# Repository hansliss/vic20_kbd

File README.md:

# vic20_kbd
A Cherry MX based keyboard for the VIC-20/C64, using the same matrix/interface, and aiming for the same form factor.

SHIFT LOCK is implemented with a flip-flop instead of a toggling switch.

The anti-ghosting diodes are probably not really needed, I just thought it SHOULD have them. Have fun soldering!

I use a normal 2.54mm pitch single-row pin header socket for the keyboard connector, with the cables soldered on, secured with shrink tubing and hot glue. This seems sturdy enough. Plug pin #2, the key pin, with something.

Print the stem adapters from CBMKeyAdapter.scad on an FDM printer using a .25mm nozzle. A resin printer produces better results, but the material is typically much too brittle for this kind of thing.

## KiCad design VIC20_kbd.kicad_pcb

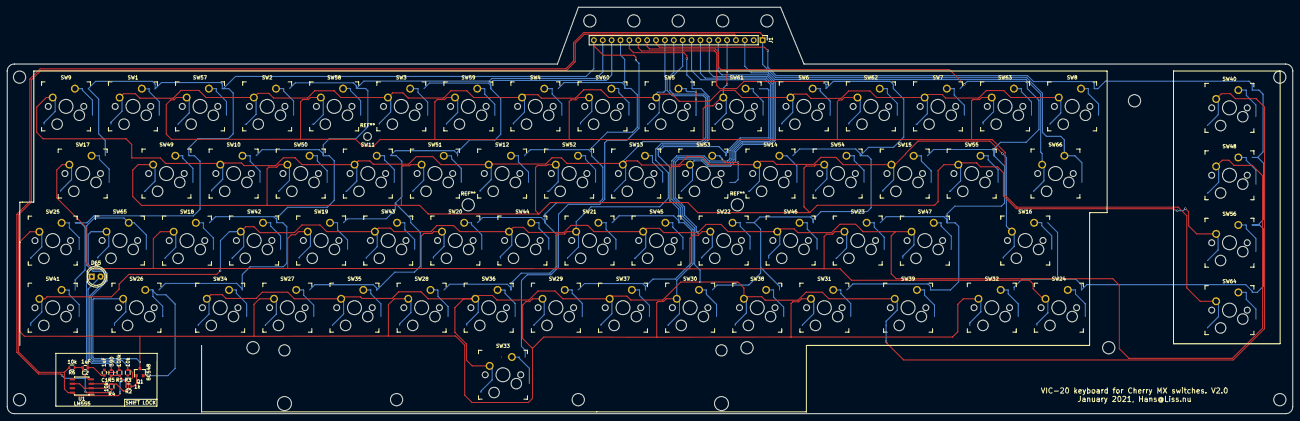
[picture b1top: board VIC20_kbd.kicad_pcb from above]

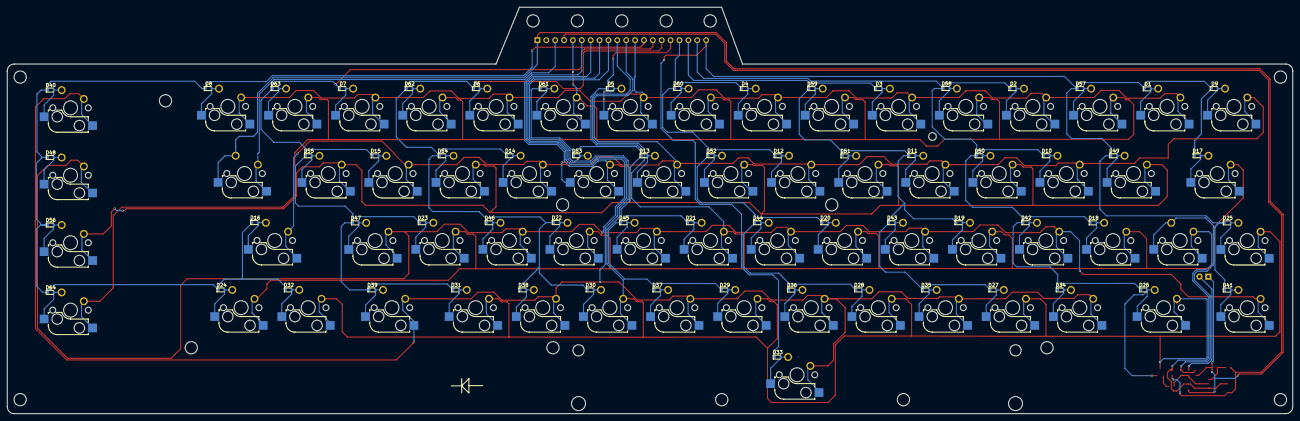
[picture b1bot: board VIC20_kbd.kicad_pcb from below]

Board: 2 copper layers, 367.7 x 116.2 mm, 142 parts (64 on the bottom side), 89 nets.

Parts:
C1, C2: 1uF; C_0603
D1, D2, D3, D4, D5, D6, D7, D8, D9, D10, D11, D12, D13, D14, D15, D16, D17, D18, D19, D20, D21, D22, D23, D24, D25, D26, D27, D28, D29, D30, D31, D32, D33, D34, D35, D36, D37, D38, D39, D40, D41, D42, D43, D44, D45, D46, D47, D48, D49, D50, D51, D52, D53, D54, D55, D56, D57, D58, D59, D60, D61, D62, D63, D64: D; D_0603
D65: LED; LED_D5.0mm
J1: Conn_01x20; Pin_Header_Straight_1x20_Pitch2.54mm
Q1: BC548; SOT-23
R1: 100k; R_0603
R2: 1k; R_0603
R3, R4, R6: 10k; R_0603
R5: 390; R_0603
SW1: Key_1; Kailh_socket_MX_optional_compatible
SW2: Key_3; Kailh_socket_MX_optional_compatible
SW3: Key_5; Kailh_socket_MX_optional_compatible
SW4: Key_7; Kailh_socket_MX_optional_compatible
SW5: Key_9; Kailh_socket_MX_optional_compatible
SW6: Key_Plus; Kailh_socket_MX_optional_compatible
SW7: Key_Pound; Kailh_socket_MX_optional_compatible
SW8: Key_DEL; Kailh_socket_MX_optional_compatible
SW9: Key_ARROWLEFT; Kailh_socket_MX_optional_compatible
SW10: Key_W; Kailh_socket_MX_optional_compatible
SW11: Key_R; Kailh_socket_MX_optional_compatible
SW12: Key_Y; Kailh_socket_MX_optional_compatible
SW13: Key_I; Kailh_socket_MX_optional_compatible
SW14: Key_P; Kailh_socket_MX_optional_compatible
SW15: Key_asterisk; Kailh_socket_MX_optional_compatible
SW16: Key_RETURN; Kailh_socket_MX_optional_compatible
SW17: Key_CTRL; Kailh_socket_MX_optional_compatible
SW18: Key_A; Kailh_socket_MX_optional_compatible
SW19: Key_D; Kailh_socket_MX_optional_compatible
SW20: Key_G; Kailh_socket_MX_optional_compatible
SW21: Key_J; Kailh_socket_MX_optional_compatible
SW22: Key_L; Kailh_socket_MX_optional_compatible
SW23: Key_semicolon; Kailh_socket_MX_optional_compatible
SW24: Key_CRSRRIGHT; Kailh_socket_MX_optional_compatible
SW25: Key_STOP; Kailh_socket_MX_optional_compatible
SW26: Key_LSHFT; Kailh_socket_MX_optional_compatible
SW27: Key_X; Kailh_socket_MX_optional_compatible
SW28: Key_V; Kailh_socket_MX_optional_compatible
SW29: Key_N; Kailh_socket_MX_optional_compatible
SW30: Key_comma; Kailh_socket_MX_optional_compatible
SW31: Key_slash; Kailh_socket_MX_optional_compatible
SW32: Key_CRSRDOWN; Kailh_socket_MX_optional_compatible
SW33: Key_SPACE; Kailh_socket_MX_optional_compatible
SW34: Key_Z; Kailh_socket_MX_optional_compatible
SW35: Key_C; Kailh_socket_MX_optional_compatible
SW36: Key_B; Kailh_socket_MX_optional_compatible
SW37: Key_M; Kailh_socket_MX_optional_compatible
SW38: Key_period; Kailh_socket_MX_optional_compatible
SW39: Key_RSHFT; Kailh_socket_MX_optional_compatible
SW40: Key_F1; Kailh_socket_MX_optional_compatible
SW41: Key_CBM; Kailh_socket_MX_optional_compatible
SW42: Key_S; Kailh_socket_MX_optional_compatible
SW43: Key_F; Kailh_socket_MX_optional_compatible
SW44: Key_H; Kailh_socket_MX_optional_compatible
SW45: Key_K; Kailh_socket_MX_optional_compatible
SW46: Key_colon; Kailh_socket_MX_optional_compatible
SW47: Key_equals; Kailh_socket_MX_optional_compatible
SW48: Key_F3; Kailh_socket_MX_optional_compatible
SW49: Key_Q; Kailh_socket_MX_optional_compatible
SW50: Key_E; Kailh_socket_MX_optional_compatible
SW51: Key_T; Kailh_socket_MX_optional_compatible
SW52: Key_U; Kailh_socket_MX_optional_compatible
SW53: Key_O; Kailh_socket_MX_optional_compatible
SW54: Key_at; Kailh_socket_MX_optional_compatible
SW55: Key_ARROWUP; Kailh_socket_MX_optional_compatible
SW56: Key_F5; Kailh_socket_MX_optional_compatible
SW57: Key_2; Kailh_socket_MX_optional_compatible
SW58: Key_4; Kailh_socket_MX_optional_compatible
SW59: Key_6; Kailh_socket_MX_optional_compatible
SW60: Key_8; Kailh_socket_MX_optional_compatible
SW61: Key_0; Kailh_socket_MX_optional_compatible
SW62: Key_minus; Kailh_socket_MX_optional_compatible
SW63: Key_HOME; Kailh_socket_MX_optional_compatible
SW64: Key_F7; Kailh_socket_MX_optional_compatible
SW65: Key_SHFTLCK; Kailh_socket_MX_optional_compatible
SW66: Key_RESTORE; Kailh_socket_MX_optional_compatible
U1: LM555; SOIC-8_3.9x4.9mm_Pitch1.27mm

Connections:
/C0: J1.12, SW1.2, SW2.2, SW3.2, SW4.2, SW5.2, SW6.2, SW7.2, SW8.2
/C1: J1.11, SW9.2, SW10.2, SW11.2, SW12.2, SW13.2, SW14.2, SW15.2, SW16.2
/C2: J1.10, SW17.2, SW18.2, SW19.2, SW20.2, SW21.2, SW22.2, SW23.2, SW24.2
/C3: J1.9, Q1.3, SW25.2, SW26.2, SW27.2, SW28.2, SW29.2, SW30.2, SW31.2, SW32.2
/C4: J1.8, SW33.2, SW34.2, SW35.2, SW36.2, SW37.2, SW38.2, SW39.2, SW40.2
/C5: J1.7, SW41.2, SW42.2, SW43.2, SW44.2, SW45.2, SW46.2, SW47.2, SW48.2
/C6: J1.6, SW49.2, SW50.2, SW51.2, SW52.2, SW53.2, SW54.2, SW55.2, SW56.2
/C7: J1.5, SW57.2, SW58.2, SW59.2, SW60.2, SW61.2, SW62.2, SW63.2, SW64.2
/R8: J1.3, SW66.2
/RA: D1.1, D9.1, D17.1, D25.1, D33.1, D41.1, D49.1, D57.1, J1.20
/RB: D2.1, D10.1, D18.1, D26.1, D34.1, D42.1, D50.1, D58.1, J1.19
/RC: D3.1, D11.1, D19.1, D27.1, D35.1, D43.1, D51.1, D59.1, J1.18
/RD: D4.1, D12.1, D20.1, D28.1, D36.1, D44.1, D52.1, D60.1, J1.17
/RE: D5.1, D13.1, D21.1, D29.1, D37.1, D45.1, D53.1, D61.1, J1.16
/RF: D6.1, D14.1, D22.1, D30.1, D38.1, D46.1, D54.1, D62.1, J1.15
/RG: D7.1, D15.1, D23.1, D31.1, D39.1, D47.1, D55.1, D63.1, J1.14
/RH: D8.1, D16.1, D24.1, D32.1, D40.1, D48.1, D56.1, D64.1, J1.13
GND: C1.2, C2.2, D65.1, J1.1, R4.2, SW66.1, U1.1
unnamed: C1.1, R1.2, SW65.1
unnamed: C2.1, R6.2, U1.4
unnamed: D1.2, SW1.1
unnamed: D2.2, SW2.1
unnamed: D3.2, SW3.1
unnamed: D4.2, SW4.1
unnamed: D5.2, SW5.1
unnamed: D6.2, SW6.1
unnamed: D7.2, SW7.1
unnamed: D8.2, SW8.1
unnamed: D9.2, SW9.1
unnamed: D10.2, SW10.1
unnamed: D11.2, SW11.1
unnamed: D12.2, SW12.1
unnamed: D13.2, SW13.1
unnamed: D14.2, SW14.1
unnamed: D15.2, SW15.1
unnamed: D16.2, SW16.1
unnamed: D17.2, SW17.1
unnamed: D18.2, SW18.1
unnamed: D19.2, SW19.1
unnamed: D20.2, SW20.1
unnamed: D21.2, SW21.1
unnamed: D22.2, SW22.1
unnamed: D23.2, SW23.1
unnamed: D24.2, SW24.1
unnamed: D25.2, SW25.1
unnamed: D26.2, Q1.2, SW26.1
unnamed: D27.2, SW27.1
unnamed: D28.2, SW28.1
unnamed: D29.2, SW29.1
unnamed: D30.2, SW30.1
unnamed: D31.2, SW31.1
unnamed: D32.2, SW32.1
unnamed: D33.2, SW33.1
unnamed: D34.2, SW34.1
unnamed: D35.2, SW35.1
unnamed: D36.2, SW36.1
unnamed: D37.2, SW37.1
unnamed: D38.2, SW38.1
unnamed: D39.2, SW39.1
unnamed: D40.2, SW40.1
unnamed: D41.2, SW41.1
unnamed: D42.2, SW42.1
unnamed: D43.2, SW43.1
unnamed: D44.2, SW44.1
unnamed: D45.2, SW45.1
unnamed: D46.2, SW46.1
unnamed: D47.2, SW47.1
unnamed: D48.2, SW48.1
unnamed: D49.2, SW49.1
unnamed: D50.2, SW50.1
unnamed: D51.2, SW51.1
unnamed: D52.2, SW52.1
unnamed: D53.2, SW53.1
unnamed: D54.2, SW54.1
unnamed: D55.2, SW55.1
unnamed: D56.2, SW56.1
unnamed: D57.2, SW57.1
unnamed: D58.2, SW58.1
unnamed: D59.2, SW59.1
unnamed: D60.2, SW60.1
unnamed: D61.2, SW61.1
unnamed: D62.2, SW62.1
unnamed: D63.2, SW63.1
unnamed: D64.2, SW64.1
unnamed: D65.2, R5.2
unnamed: Q1.1, R2.1
unnamed: R1.1, R2.2, R5.1, U1.3
unnamed: R3.1, R4.1, SW65.2, U1.2, U1.6
VCC: J1.4, R3.2, R6.1, U1.8

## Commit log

2019-06-05 Initial import
2019-06-06 Added rounded corners Added mounting holes and cables support holes
2019-06-09 Rerouted everything, tidier V1.2
2020-03-06 Added SHIFT LOCK flip-flop to PCB Added Gerber files
2020-03-07 Added key stem adapter source code.
2020-09-28 Added simple mounting brackets in OpenSCAD format. Added sym-lib-table.
2021-01-09 Cleaned up to accommodate Kailh sockets.
2021-01-09 Cleaned up SHIFT LOCK area and fixed silkscreen.
2021-01-09 Additional preparation for Kailh sockets
2021-01-09 Kailh sockets A big diode symbol on bottom silkscreen layer, as a guide.
